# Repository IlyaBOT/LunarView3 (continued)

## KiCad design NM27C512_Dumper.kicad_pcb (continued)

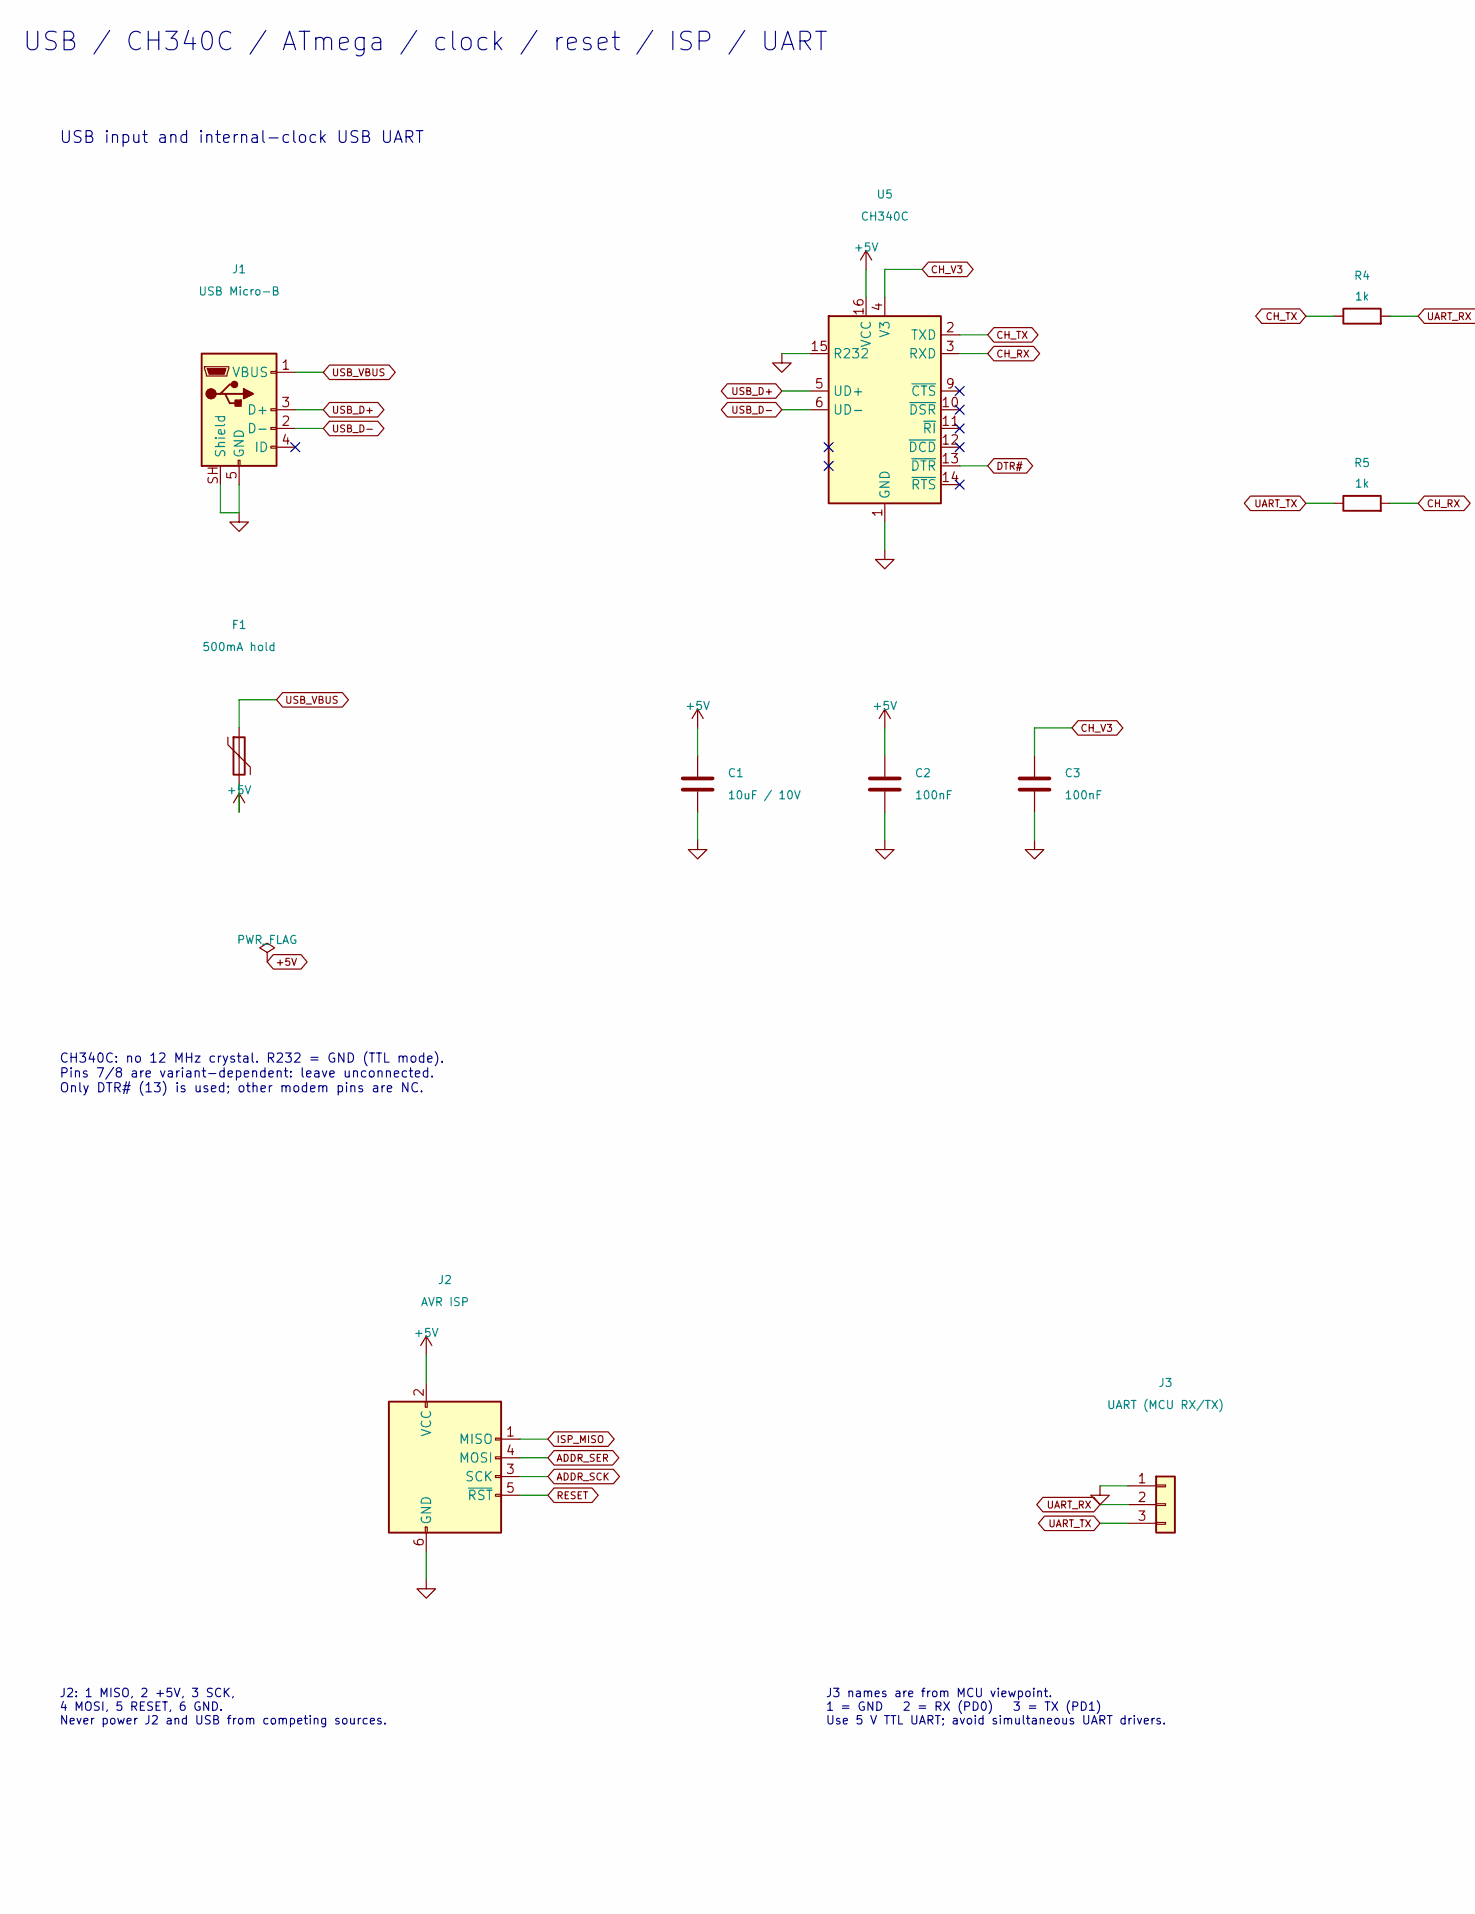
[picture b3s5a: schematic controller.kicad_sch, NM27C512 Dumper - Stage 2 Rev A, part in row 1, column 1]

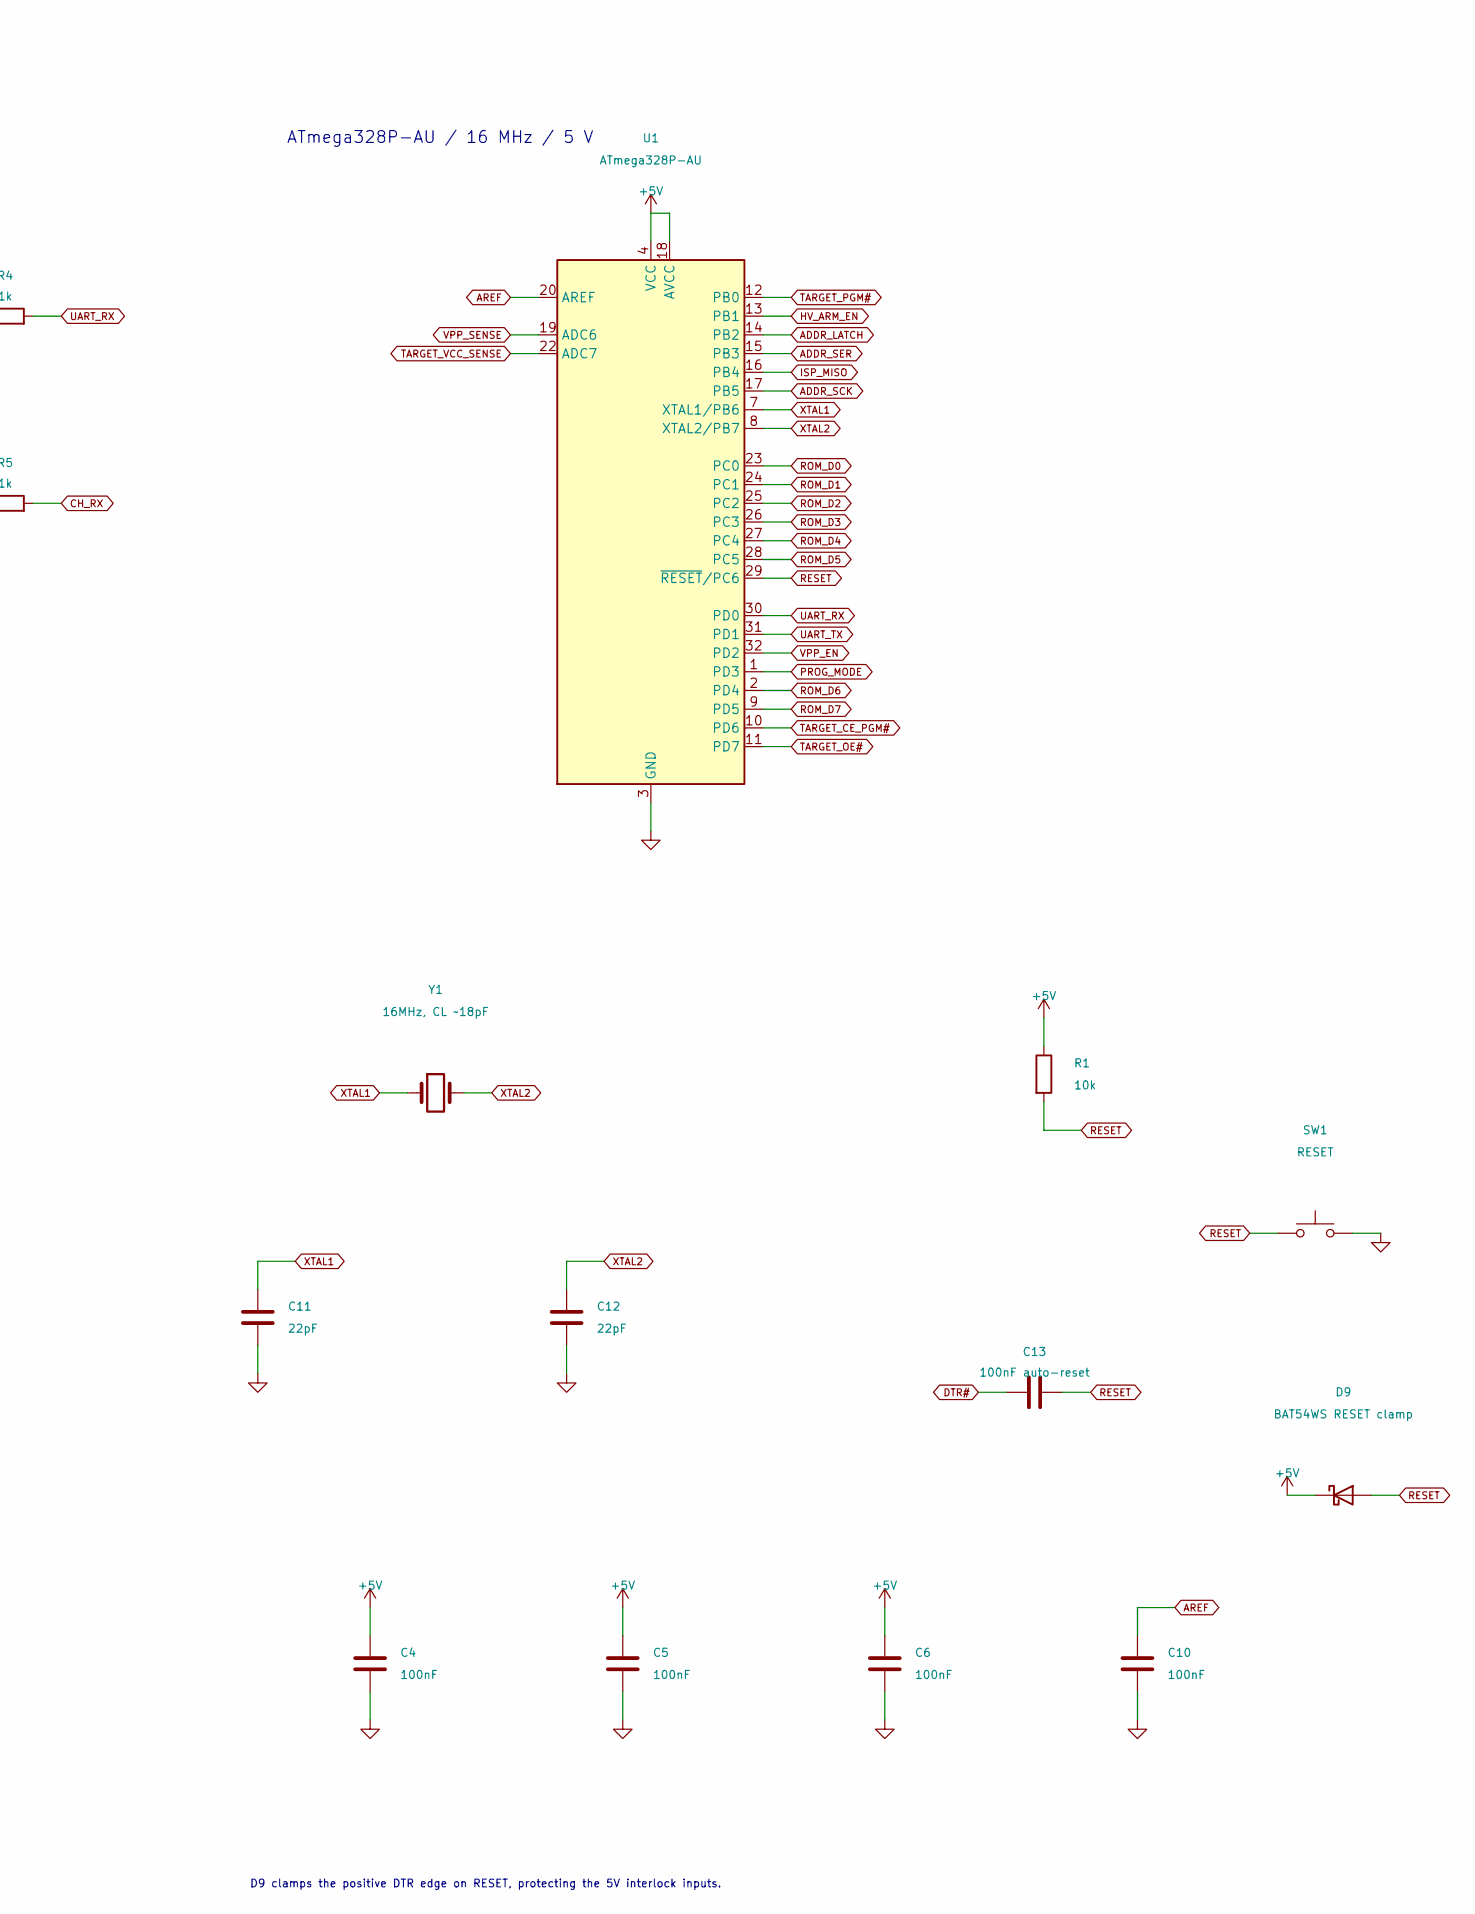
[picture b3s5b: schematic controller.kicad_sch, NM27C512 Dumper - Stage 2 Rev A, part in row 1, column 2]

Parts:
C1: 10uF / 10V; C_0805_2012Metric
C2, C3, C4, C5, C6, C10: 100nF; C_0603_1608Metric
C11, C12: 22pF; C_0603_1608Metric
C13: 100nF auto-reset; C_0603_1608Metric
D9: BAT54WS RESET clamp; D_SOD-323
F1: 500mA hold; Fuse_1812_4532Metric
J1: USB Micro-B; USB_Micro-B_Molex-105017-0001
J2: AVR ISP; PinHeader_2x03_P2.54mm_Vertical
J3: UART (MCU RX/TX); PinHeader_1x03_P2.54mm_Vertical
R1: 10k; R_0603_1608Metric
R4, R5: 1k; R_0603_1608Metric
SW1: RESET; SW_PUSH_6mm
U1: ATmega328P-AU; TQFP-32_7x7mm_P0.8mm
U5: CH340C; SOIC-16_3.9x9.9mm_P1.27mm
Y1: 16MHz, CL ~18pF; Crystal_HC49-4H_Vertical

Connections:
+5V: C1.1, C2.1, C4.1, C5.1, C6.1, D9.1 (K), F1.2, J2.2 (VCC), R1.1, U1.4 (VCC), U1.6 (VCC), U1.18 (AVCC), U5.16 (VCC); also elsewhere on the board
ADDR_LATCH: U1.14 (PB2); also elsewhere on the board
ADDR_SCK: J2.3 (SCK), U1.17 (PB5); also elsewhere on the board
ADDR_SER: J2.4 (MOSI), U1.15 (PB3); also elsewhere on the board
AREF: C10.1, U1.20 (AREF)
CH_RX: R5.2, U5.3 (RXD)
CH_TX: R4.1, U5.2 (TXD)
CH_V3: C3.1, U5.4 (V3)
DTR#: C13.1, U5.13 (~DTR)
GND: C1.2, C2.2, C3.2, C4.2, C5.2, C6.2, C10.2, C11.2, C12.2, J1.5 (GND), J1.SH (Shield), J2.6 (GND), J3.1, SW1.2, U1.3 (GND), U1.5 (GND), U1.21 (GND), U5.1 (GND), U5.15 (R232); also elsewhere on the board
HV_ARM_EN: U1.13 (PB1); also elsewhere on the board
ISP_MISO: J2.1 (MISO), U1.16 (PB4)
PROG_MODE: U1.1 (PD3); also elsewhere on the board
RESET: C13.2, D9.2 (A), J2.5 (~RST), R1.2, SW1.1, U1.29 (~RESET/PC6); also elsewhere on the board
ROM_D0: U1.23 (PC0); also elsewhere on the board
ROM_D1: U1.24 (PC1); also elsewhere on the board
ROM_D2: U1.25 (PC2); also elsewhere on the board
ROM_D3: U1.26 (PC3); also elsewhere on the board
ROM_D4: U1.27 (PC4); also elsewhere on the board
ROM_D5: U1.28 (PC5); also elsewhere on the board
ROM_D6: U1.2 (PD4); also elsewhere on the board
ROM_D7: U1.9 (PD5); also elsewhere on the board
TARGET_CE_PGM#: U1.10 (PD6); also elsewhere on the board
TARGET_OE#: U1.11 (PD7); also elsewhere on the board
TARGET_PGM#: U1.12 (PB0); also elsewhere on the board
TARGET_VCC_SENSE: U1.22 (ADC7); also elsewhere on the board
UART_RX: J3.2, R4.2, U1.30 (PD0); also elsewhere on the board
UART_TX: J3.3, R5.1, U1.31 (PD1); also elsewhere on the board
USB_D+: J1.3 (D+), U5.5 (UD+)
USB_D-: J1.2 (D-), U5.6 (UD-)
USB_VBUS: F1.1, J1.1 (VBUS)
VPP_EN: U1.32 (PD2); also elsewhere on the board
VPP_SENSE: U1.19 (ADC6); also elsewhere on the board
XTAL1: C11.1, U1.7 (XTAL1/PB6), Y1.1
XTAL2: C12.1, U1.8 (XTAL2/PB7), Y1.2

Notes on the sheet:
J3 names are from MCU viewpoint. 1 = GND 2 = RX (PD0) 3 = TX (PD1) Use 5 V TTL UART; avoid simultaneous UART drivers.
J2: 1 MISO, 2 +5V, 3 SCK, 4 MOSI, 5 RESET, 6 GND. Never power J2 and USB from competing sources.
USB / CH340C / ATmega / clock / reset / ISP / UART
CH340C: no 12 MHz crystal. R232 = GND (TTL mode). Pins 7/8 are variant-dependent: leave unconnected. Only DTR# (13) is used; other modem pins are NC.
D9 clamps the positive DTR edge on RESET, protecting the 5V interlock inputs.
ATmega328P-AU / 16 MHz / 5 V
USB input and internal-clock USB UART

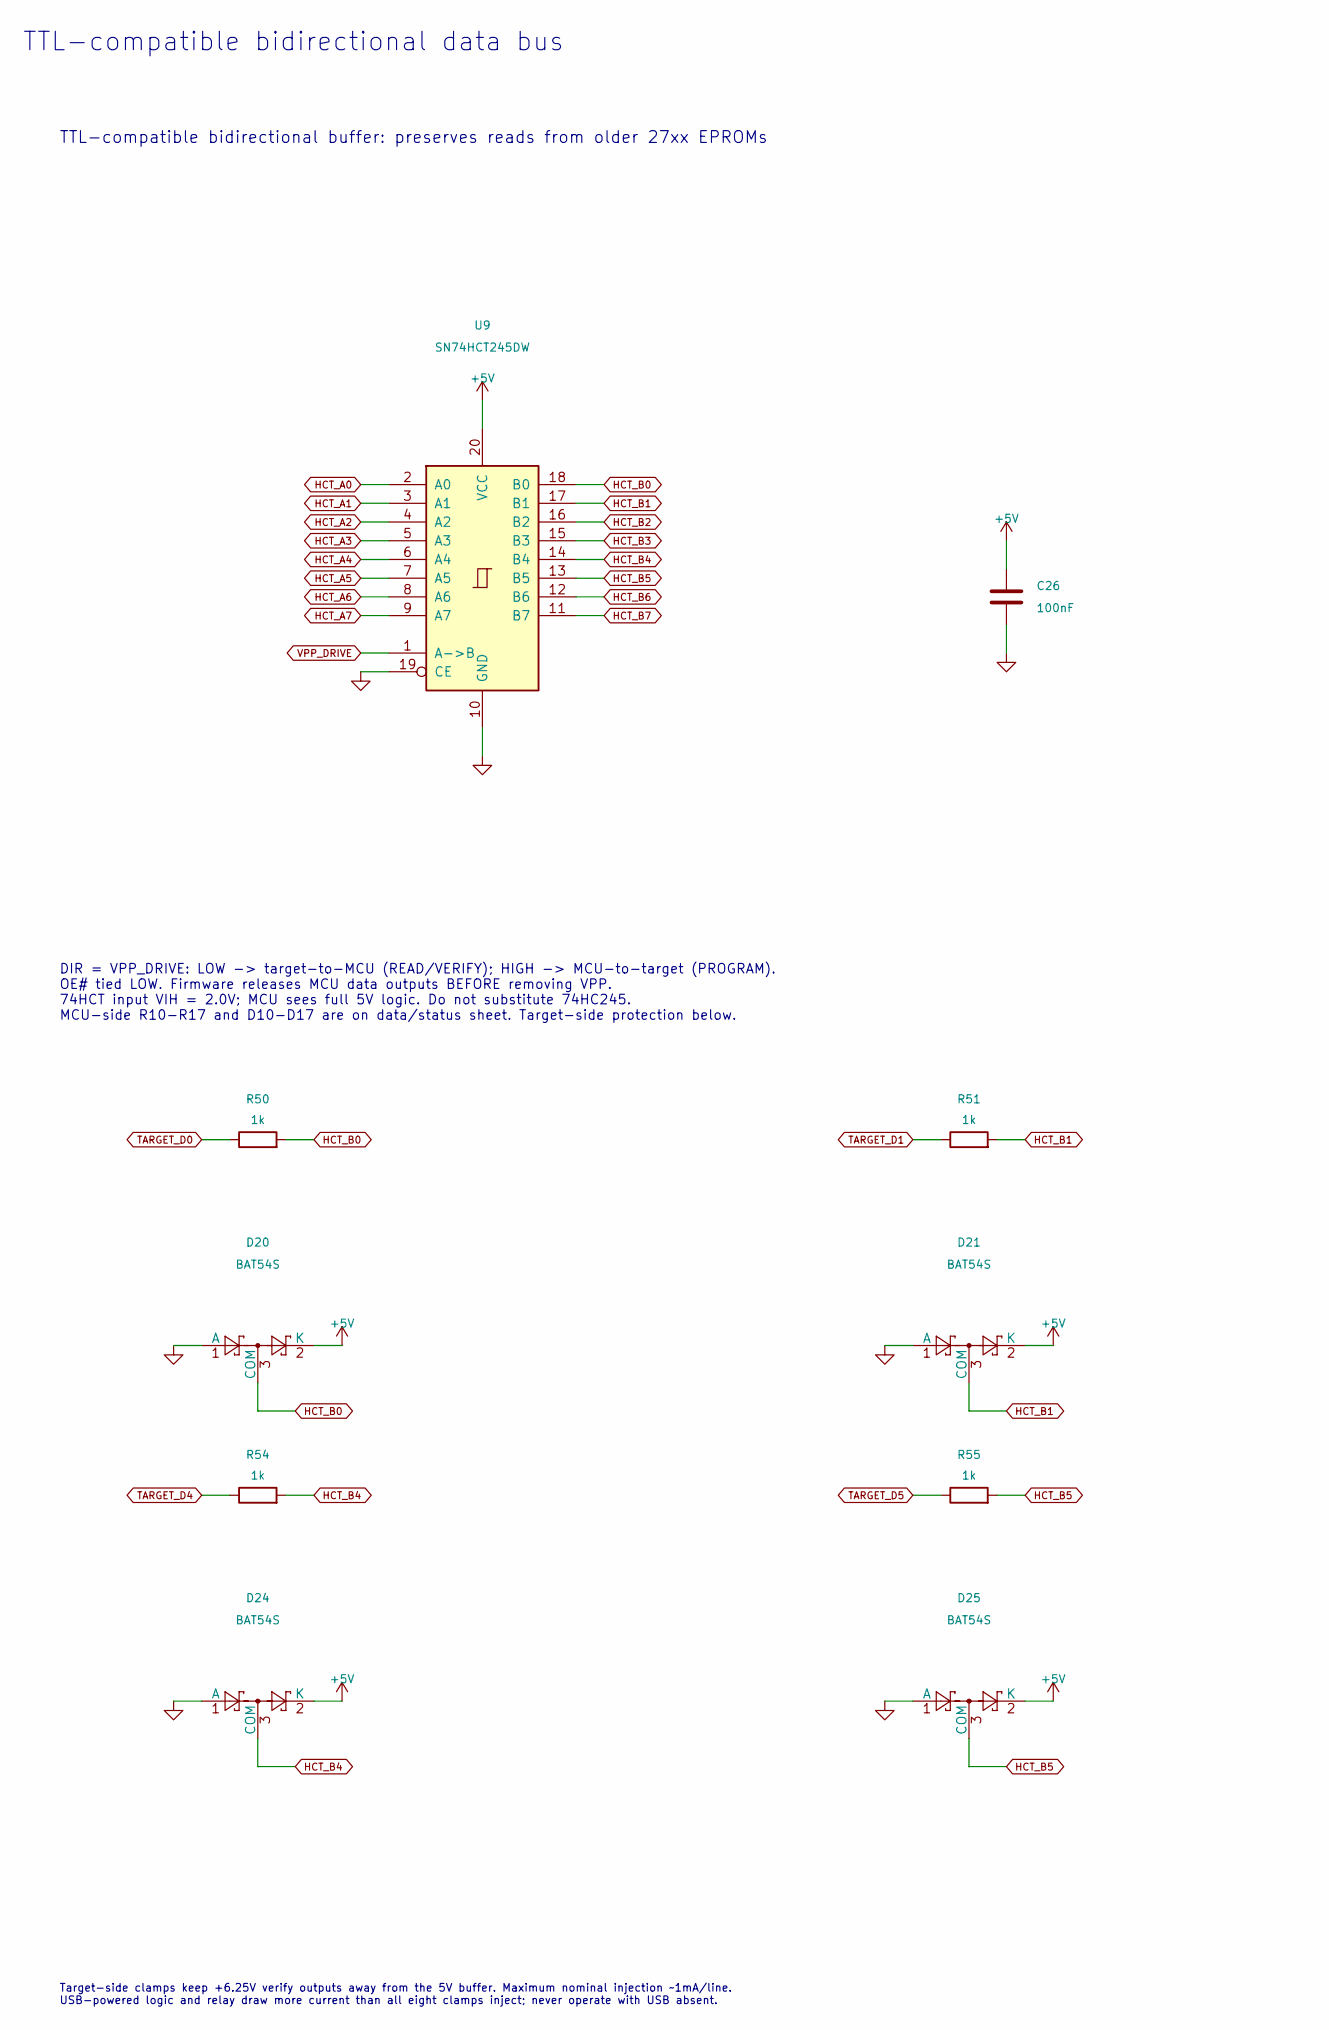
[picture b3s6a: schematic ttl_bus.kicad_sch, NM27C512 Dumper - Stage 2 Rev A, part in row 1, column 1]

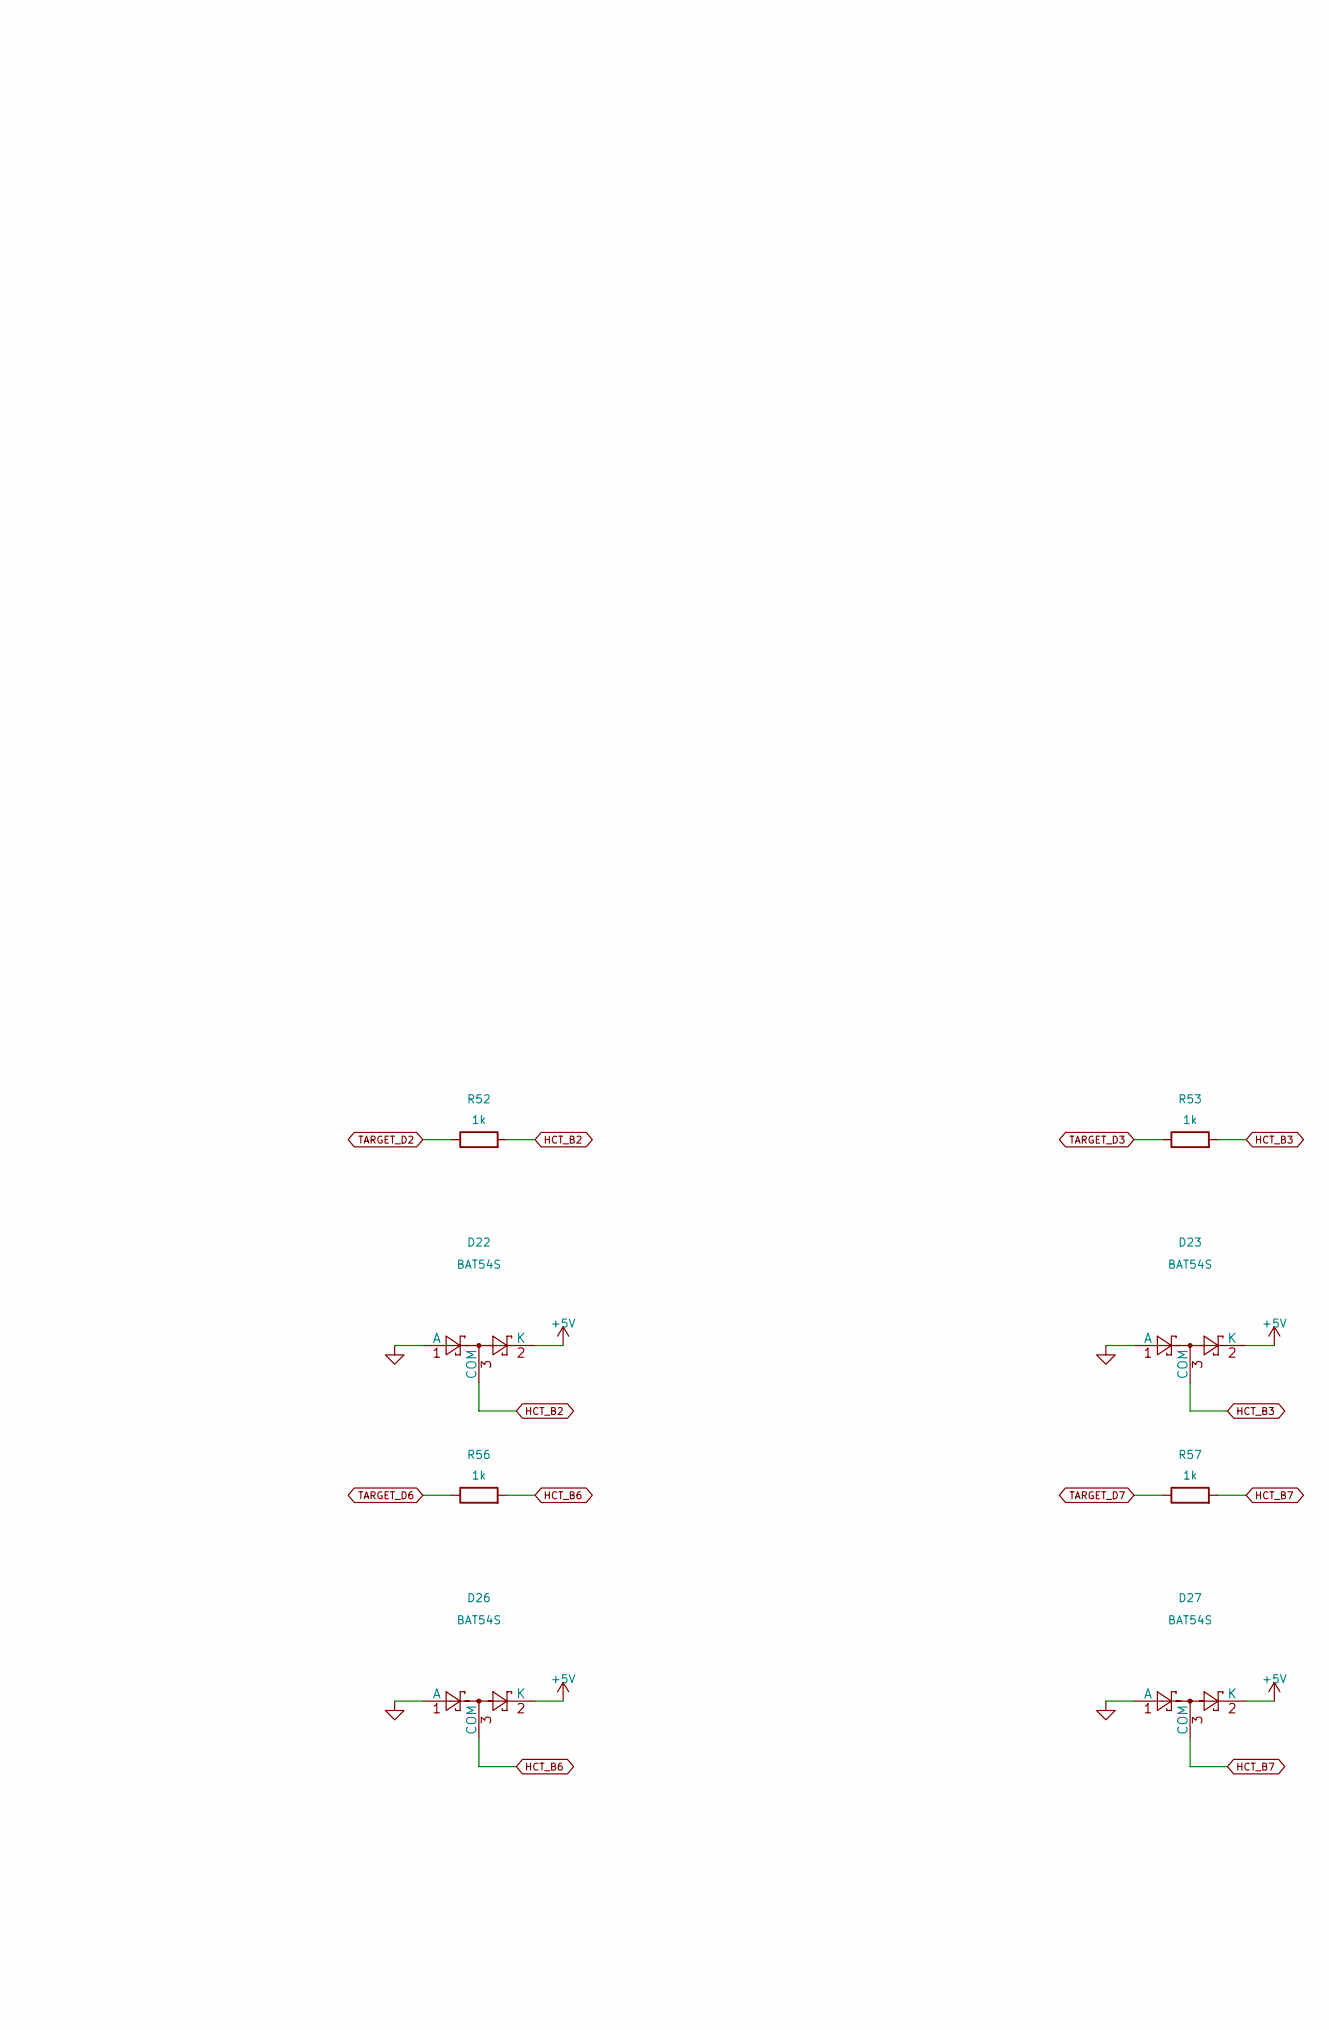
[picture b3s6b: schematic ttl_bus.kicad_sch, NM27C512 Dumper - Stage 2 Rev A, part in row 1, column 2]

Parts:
C26: 100nF; C_0603_1608Metric
D20, D21, D22, D23, D24, D25, D26, D27: BAT54S; SOT-23
R50, R51, R52, R53, R54, R55, R56, R57: 1k; R_0603_1608Metric
U9: SN74HCT245DW; SOIC-20W_7.5x12.8mm_P1.27mm

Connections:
+5V: C26.1, D20.2 (K), D21.2 (K), D22.2 (K), D23.2 (K), D24.2 (K), D25.2 (K), D26.2 (K), D27.2 (K), U9.20 (VCC); also elsewhere on the board
GND: C26.2, D20.1 (A), D21.1 (A), D22.1 (A), D23.1 (A), D24.1 (A), D25.1 (A), D26.1 (A), D27.1 (A), U9.10 (GND), U9.19 (CE); also elsewhere on the board
HCT_A0: U9.2 (A0); also elsewhere on the board
HCT_A1: U9.3 (A1); also elsewhere on the board
HCT_A2: U9.4 (A2); also elsewhere on the board
HCT_A3: U9.5 (A3); also elsewhere on the board
HCT_A4: U9.6 (A4); also elsewhere on the board
HCT_A5: U9.7 (A5); also elsewhere on the board
HCT_A6: U9.8 (A6); also elsewhere on the board
HCT_A7: U9.9 (A7); also elsewhere on the board
HCT_B0: D20.3 (COM), R50.2, U9.18 (B0)
HCT_B1: D21.3 (COM), R51.2, U9.17 (B1)
HCT_B2: D22.3 (COM), R52.2, U9.16 (B2)
HCT_B3: D23.3 (COM), R53.2, U9.15 (B3)
HCT_B4: D24.3 (COM), R54.2, U9.14 (B4)
HCT_B5: D25.3 (COM), R55.2, U9.13 (B5)
HCT_B6: D26.3 (COM), R56.2, U9.12 (B6)
HCT_B7: D27.3 (COM), R57.2, U9.11 (B7)
TARGET_D0: R50.1; also elsewhere on the board
TARGET_D1: R51.1; also elsewhere on the board
TARGET_D2: R52.1; also elsewhere on the board
TARGET_D3: R53.1; also elsewhere on the board
TARGET_D4: R54.1; also elsewhere on the board
TARGET_D5: R55.1; also elsewhere on the board
TARGET_D6: R56.1; also elsewhere on the board
TARGET_D7: R57.1; also elsewhere on the board
VPP_DRIVE: U9.1 (A->B); also elsewhere on the board

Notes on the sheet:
TTL-compatible bidirectional data bus
TTL-compatible bidirectional buffer: preserves reads from older 27xx EPROMs
DIR = VPP_DRIVE: LOW -> target-to-MCU (READ/VERIFY); HIGH -> MCU-to-target (PROGRAM). OE# tied LOW. Firmware releases MCU data outputs BEFORE removing VPP. 74HCT input VIH = 2.0V; MCU sees full 5V logic. Do not substitute 74HC245. MCU-side R10-R17 and D10-D17 are on data/status sheet. Target-side p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
Target-side clamps keep +6.25V verify outputs away from the 5V buffer. Maximum nominal injection ~1mA/line. USB-powered logic and relay draw more current than all eight clamps inject; never operate with USB absent.

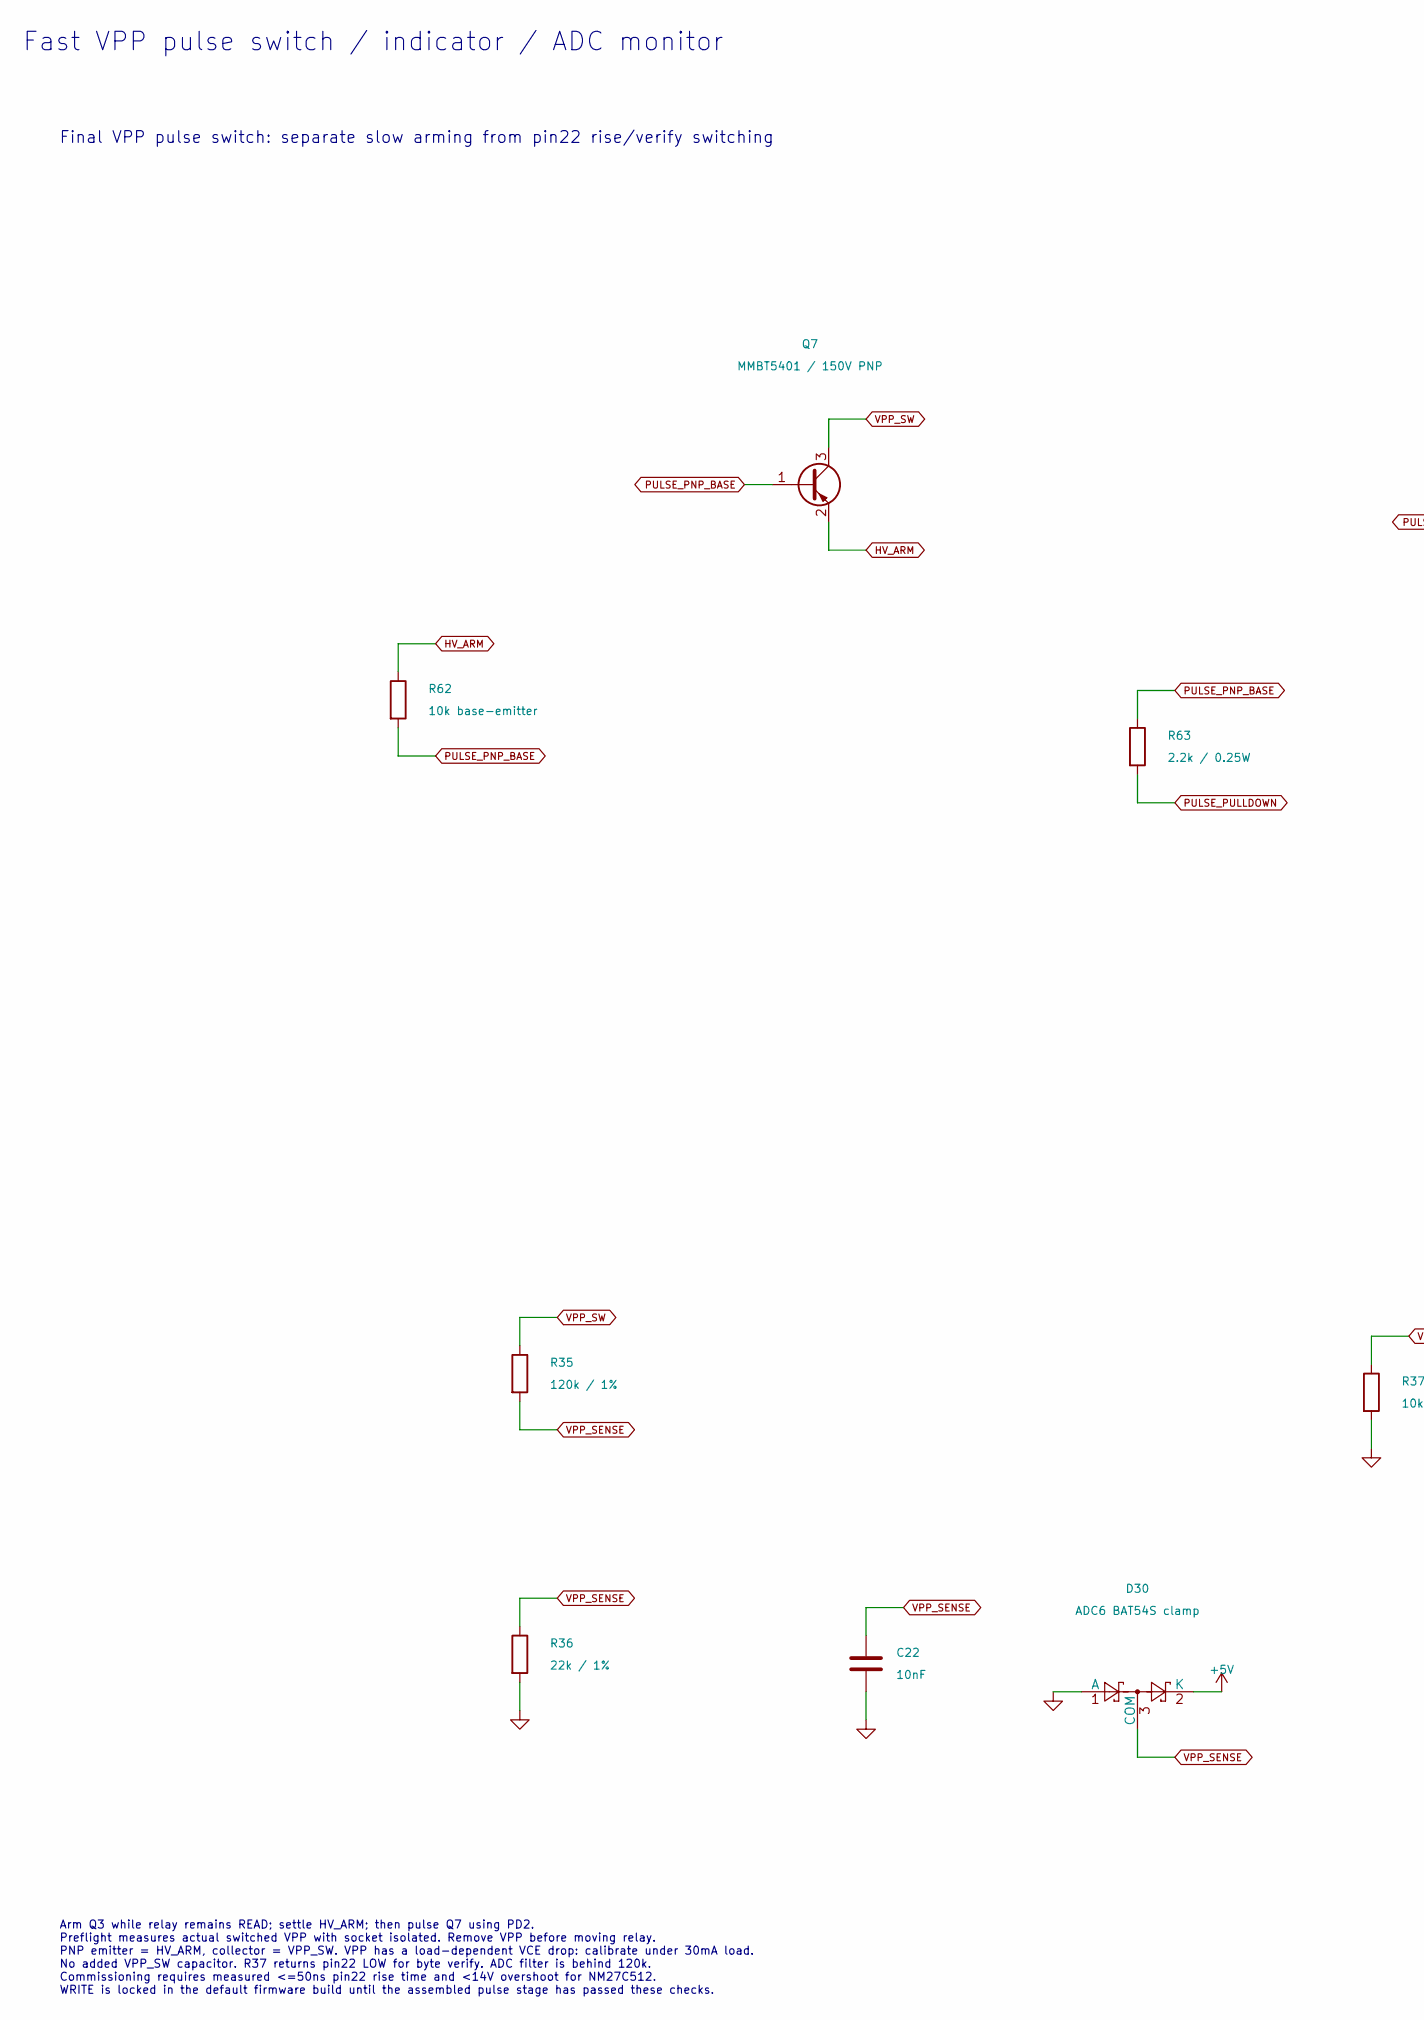
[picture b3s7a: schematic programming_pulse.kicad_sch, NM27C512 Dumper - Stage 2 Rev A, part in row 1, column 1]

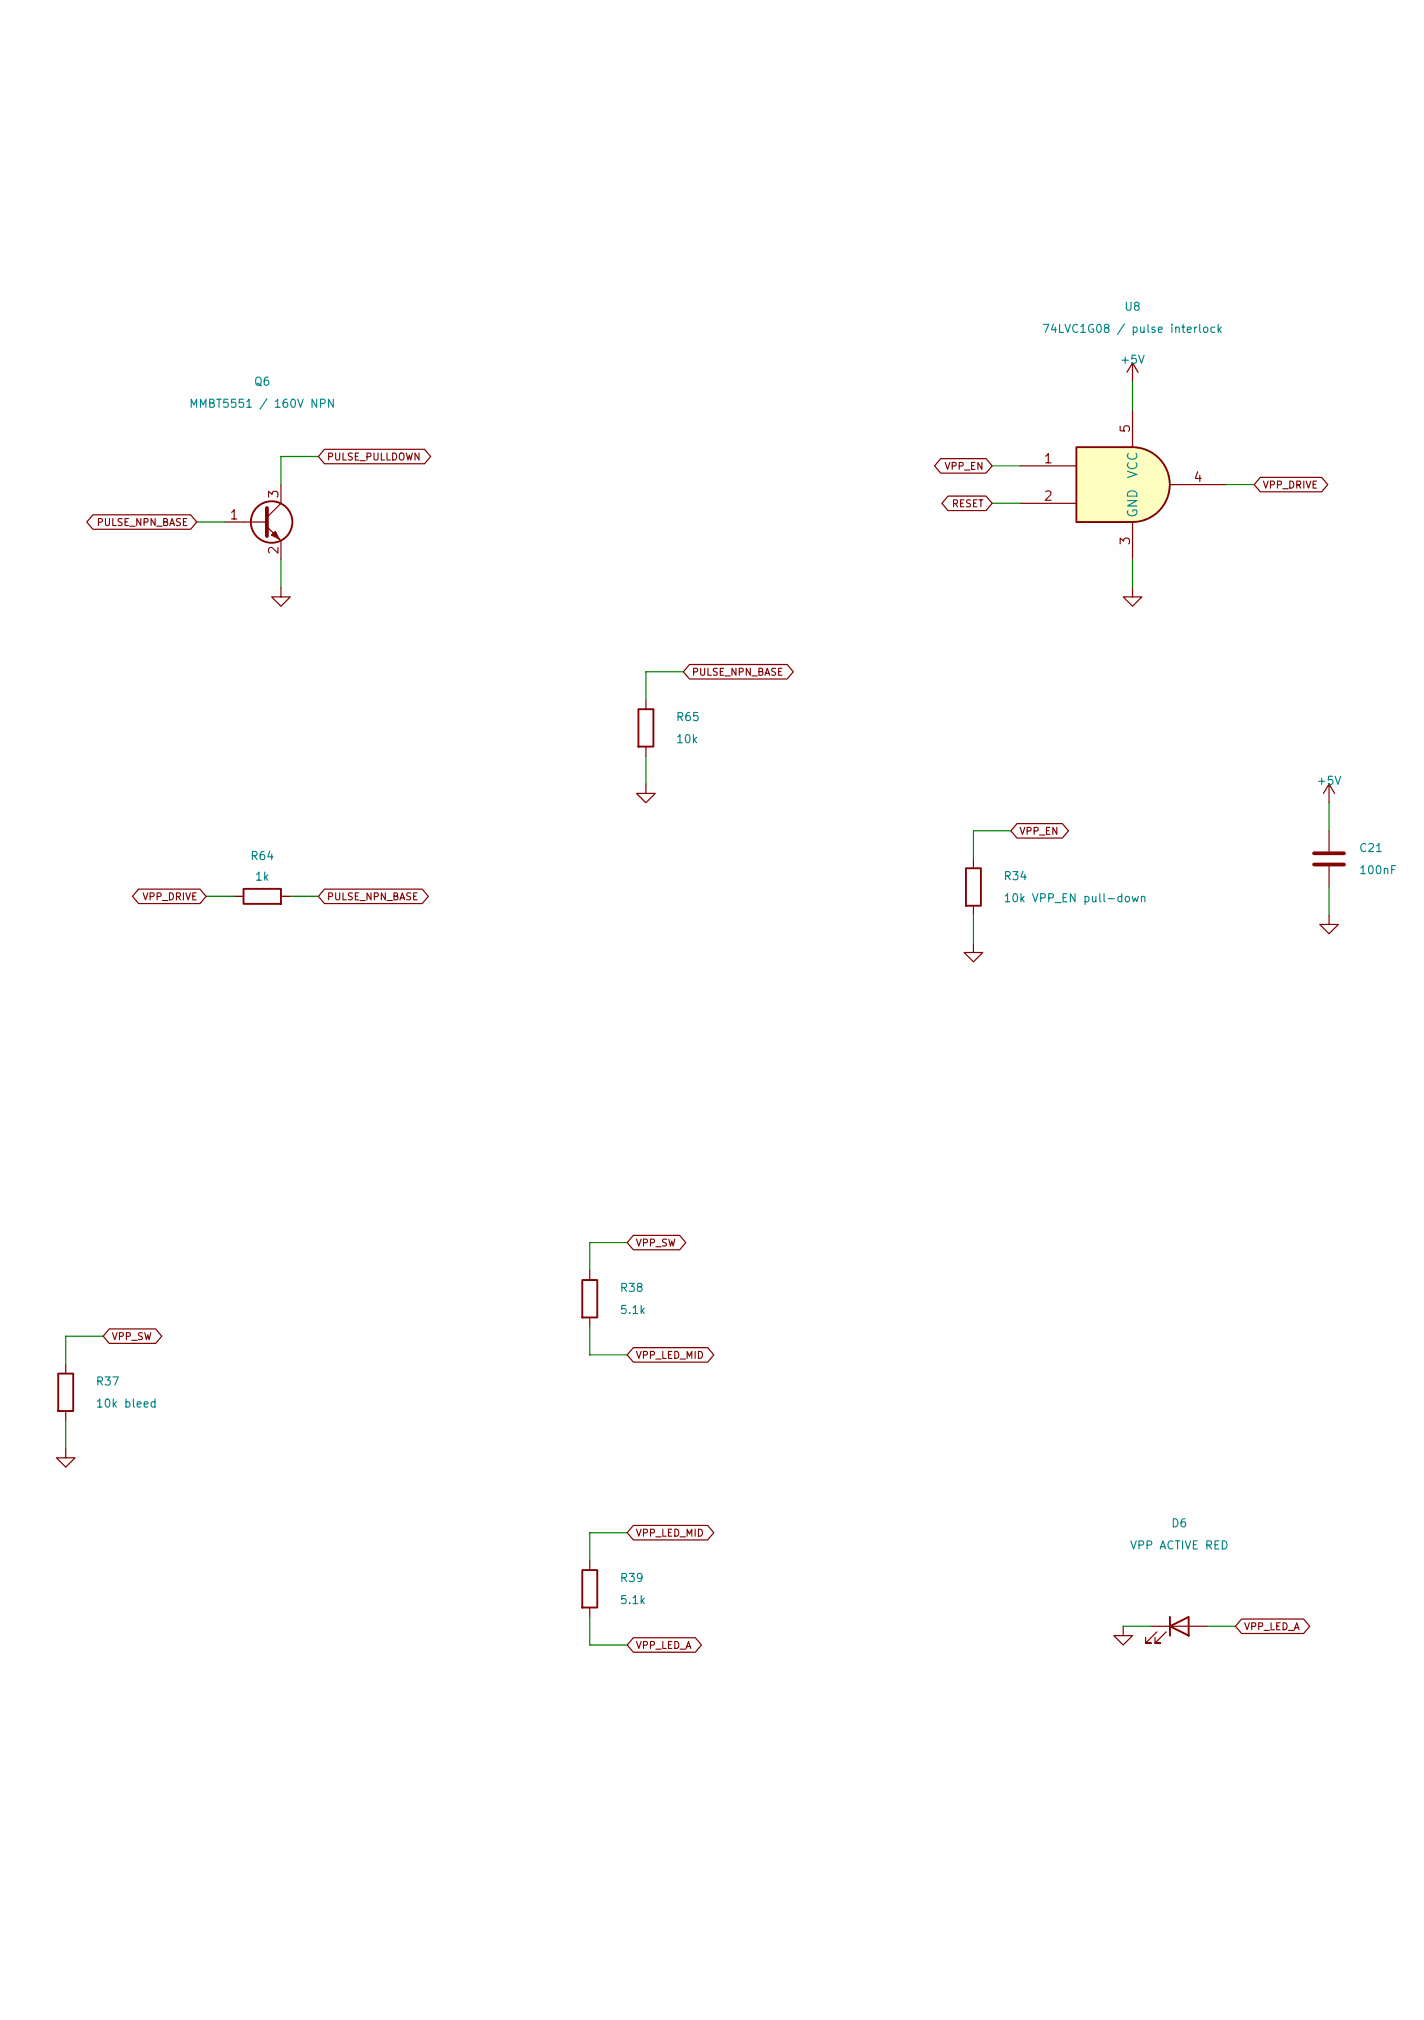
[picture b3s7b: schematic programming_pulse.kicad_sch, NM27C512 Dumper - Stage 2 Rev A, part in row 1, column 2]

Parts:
C21: 100nF; C_0603_1608Metric
C22: 10nF; C_0603_1608Metric
D6: VPP ACTIVE RED; LED_0603_1608Metric
D30: ADC6 BAT54S clamp; SOT-23
Q6: MMBT5551 / 160V NPN; SOT-23
Q7: MMBT5401 / 150V PNP; SOT-23
R34: 10k VPP_EN pull-down; R_0603_1608Metric
R35: 120k / 1%; R_0603_1608Metric
R36: 22k / 1%; R_0603_1608Metric
R37: 10k bleed; R_0603_1608Metric
R38, R39: 5.1k; R_0603_1608Metric
R62: 10k base-emitter; R_0603_1608Metric
R63: 2.2k / 0.25W; R_1206_3216Metric
R64: 1k; R_0603_1608Metric
R65: 10k; R_0603_1608Metric
U8: 74LVC1G08 / pulse interlock; SOT-23-5

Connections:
+5V: C21.1, D30.2 (K), U8.5 (VCC); also elsewhere on the board
GND: C21.2, C22.2, D6.1 (K), D30.1 (A), Q6.2 (E), R34.2, R36.2, R37.2, R65.2, U8.3 (GND); also elsewhere on the board
HV_ARM: Q7.2 (E), R62.1; also elsewhere on the board
PULSE_NPN_BASE: Q6.1 (B), R64.2, R65.1
PULSE_PNP_BASE: Q7.1 (B), R62.2, R63.1
PULSE_PULLDOWN: Q6.3 (C), R63.2
RESET: U8.2; also elsewhere on the board
VPP_DRIVE: R64.1, U8.4; also elsewhere on the board
VPP_EN: R34.1, U8.1; also elsewhere on the board
VPP_LED_A: D6.2 (A), R39.2
VPP_LED_MID: R38.2, R39.1
VPP_SENSE: C22.1, D30.3 (COM), R35.2, R36.1; also elsewhere on the board
VPP_SW: Q7.3 (C), R35.1, R37.1, R38.1; also elsewhere on the board

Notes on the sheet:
Final VPP pulse switch: separate slow arming from pin22 rise/verify switching
Fast VPP pulse switch / indicator / ADC monitor
Arm Q3 while relay remains READ; settle HV_ARM; then pulse Q7 using PD2. Preflight measures actual switched VPP with socket isolated. Remove VPP before moving relay. PNP emitter = HV_ARM, collector = VPP_SW. VPP has a load-dependent VCE drop: calibrate under 30mA load. No added VPP_SW capacitor. R3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
